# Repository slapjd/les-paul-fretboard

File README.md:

# Les Paul Fretboard PCB
PCB designed to replace the fret buttons in a GH3 Les Paul with mechanical switches and RGB LEDs

Offers a ZIF connector or 2.00mm pitch pins to connect to the rest of the guitar, depending on whether you want to use a flex-pcb ribbon cable (or something similar) or not.

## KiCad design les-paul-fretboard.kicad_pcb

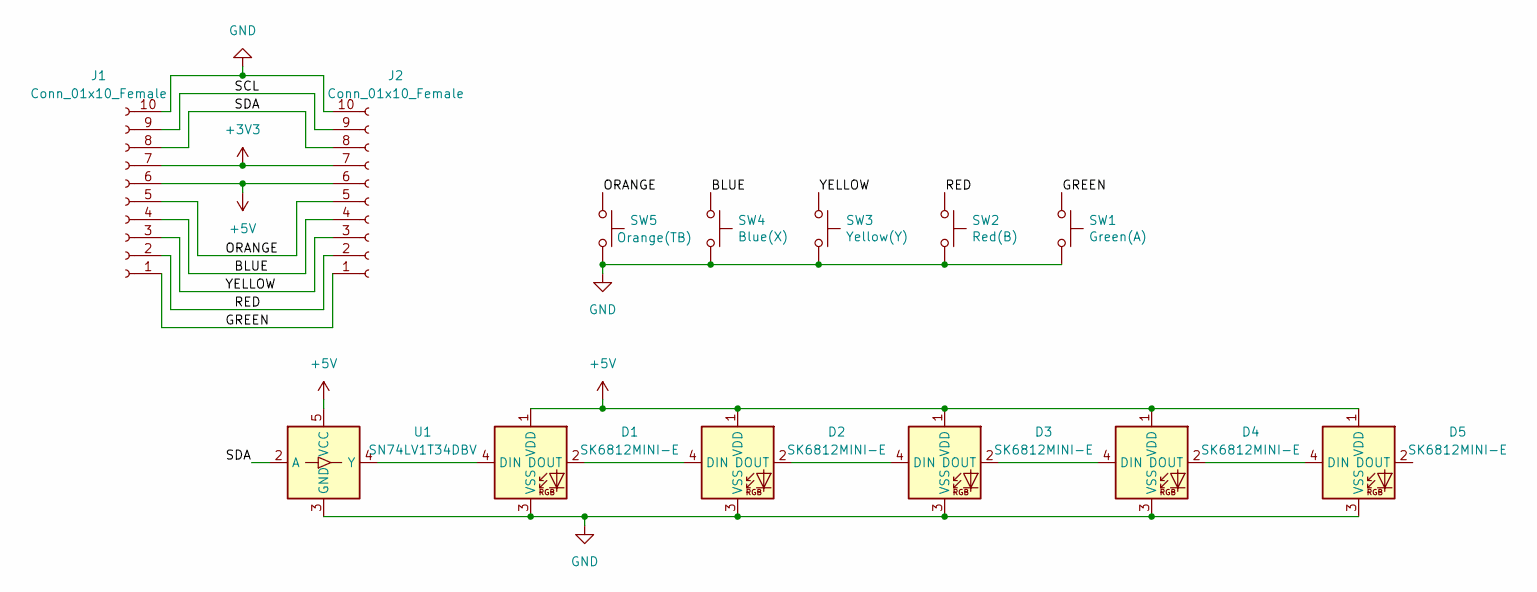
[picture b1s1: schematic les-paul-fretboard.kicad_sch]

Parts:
D1, D2, D3, D4, D5: SK6812MINI-E; SK6812MINI-E-Vias
J1: Conn_01x10_Female; Hirose_FH12-10S-0.5SH_1x10-1MP_P0.50mm_Horizontal
J2: Conn_01x10_Female; PinHeader_1x10_P2.00mm_Horizontal
SW1: Green(A); SW_Kailh_Choc_V1
SW2: Red(B); SW_Kailh_Choc_V1
SW3: Yellow(Y); SW_Kailh_Choc_V1
SW4: Blue(X); SW_Kailh_Choc_V1
SW5: Orange(TB); SW_Kailh_Choc_V1
U1: SN74LV1T34DBV; SOT-23-5

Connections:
+3V3: J1.7, J2.7
+5V: D1.1 (VDD), D2.1 (VDD), D3.1 (VDD), D4.1 (VDD), D5.1 (VDD), J1.6, J2.6, U1.5 (VCC)
/BLUE: J1.4, J2.4, SW4.1
/GREEN: J1.1, J2.1, SW1.1
/ORANGE: J1.5, J2.5, SW5.1
/RED: J1.2, J2.2, SW2.1
/SCL: J1.9, J2.9
/SDA: J1.8, J2.8, U1.2 (A)
/YELLOW: J1.3, J2.3, SW3.1
GND: D1.3 (VSS), D2.3 (VSS), D3.3 (VSS), D4.3 (VSS), D5.3 (VSS), J1.10, J2.10, SW1.2, SW2.2, SW3.2, SW4.2, SW5.2, U1.3 (GND)
unnamed: D1.2 (DOUT), D2.4 (DIN)
unnamed: D1.4 (DIN), U1.4 (Y)
unnamed: D2.2 (DOUT), D3.4 (DIN)
unnamed: D3.2 (DOUT), D4.4 (DIN)
unnamed: D4.2 (DOUT), D5.4 (DIN)

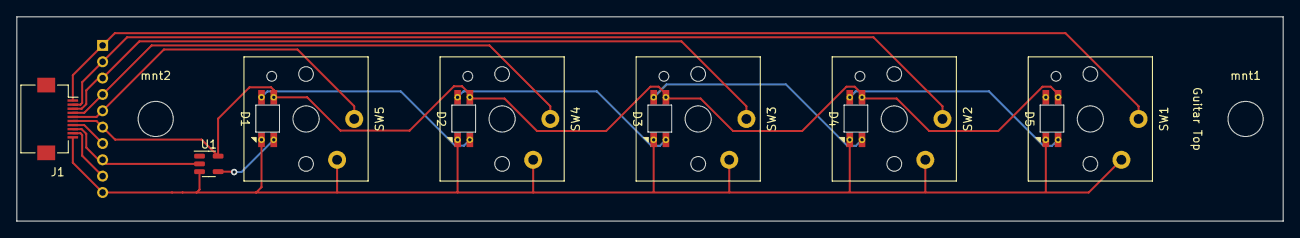
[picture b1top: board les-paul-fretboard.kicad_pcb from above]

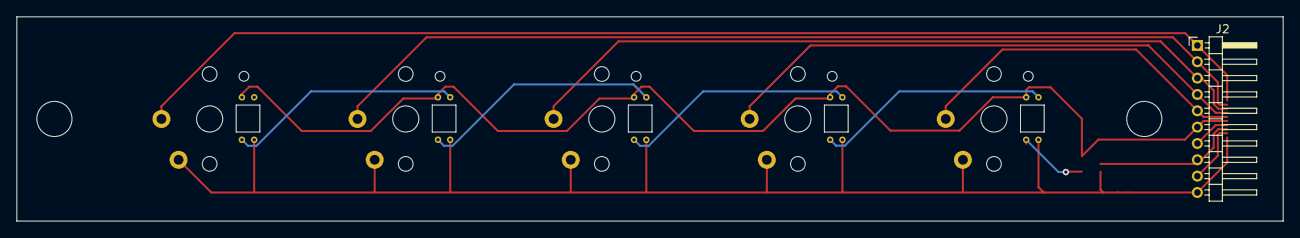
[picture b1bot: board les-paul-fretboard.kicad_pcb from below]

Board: 2 copper layers, 155.0 x 25.0 mm, 15 parts (3 on the bottom side), 15 nets.

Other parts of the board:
mnt1, mnt2: MountingHole_4.3mm_M4

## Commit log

2022-05-06 Add existing work to git
2022-05-06 README file
2022-05-06 Create LICENSE
2022-08-05 Replace LED footprint with intended footprint (pin layout was wrong)
2022-08-05 Include semi-custom led library
